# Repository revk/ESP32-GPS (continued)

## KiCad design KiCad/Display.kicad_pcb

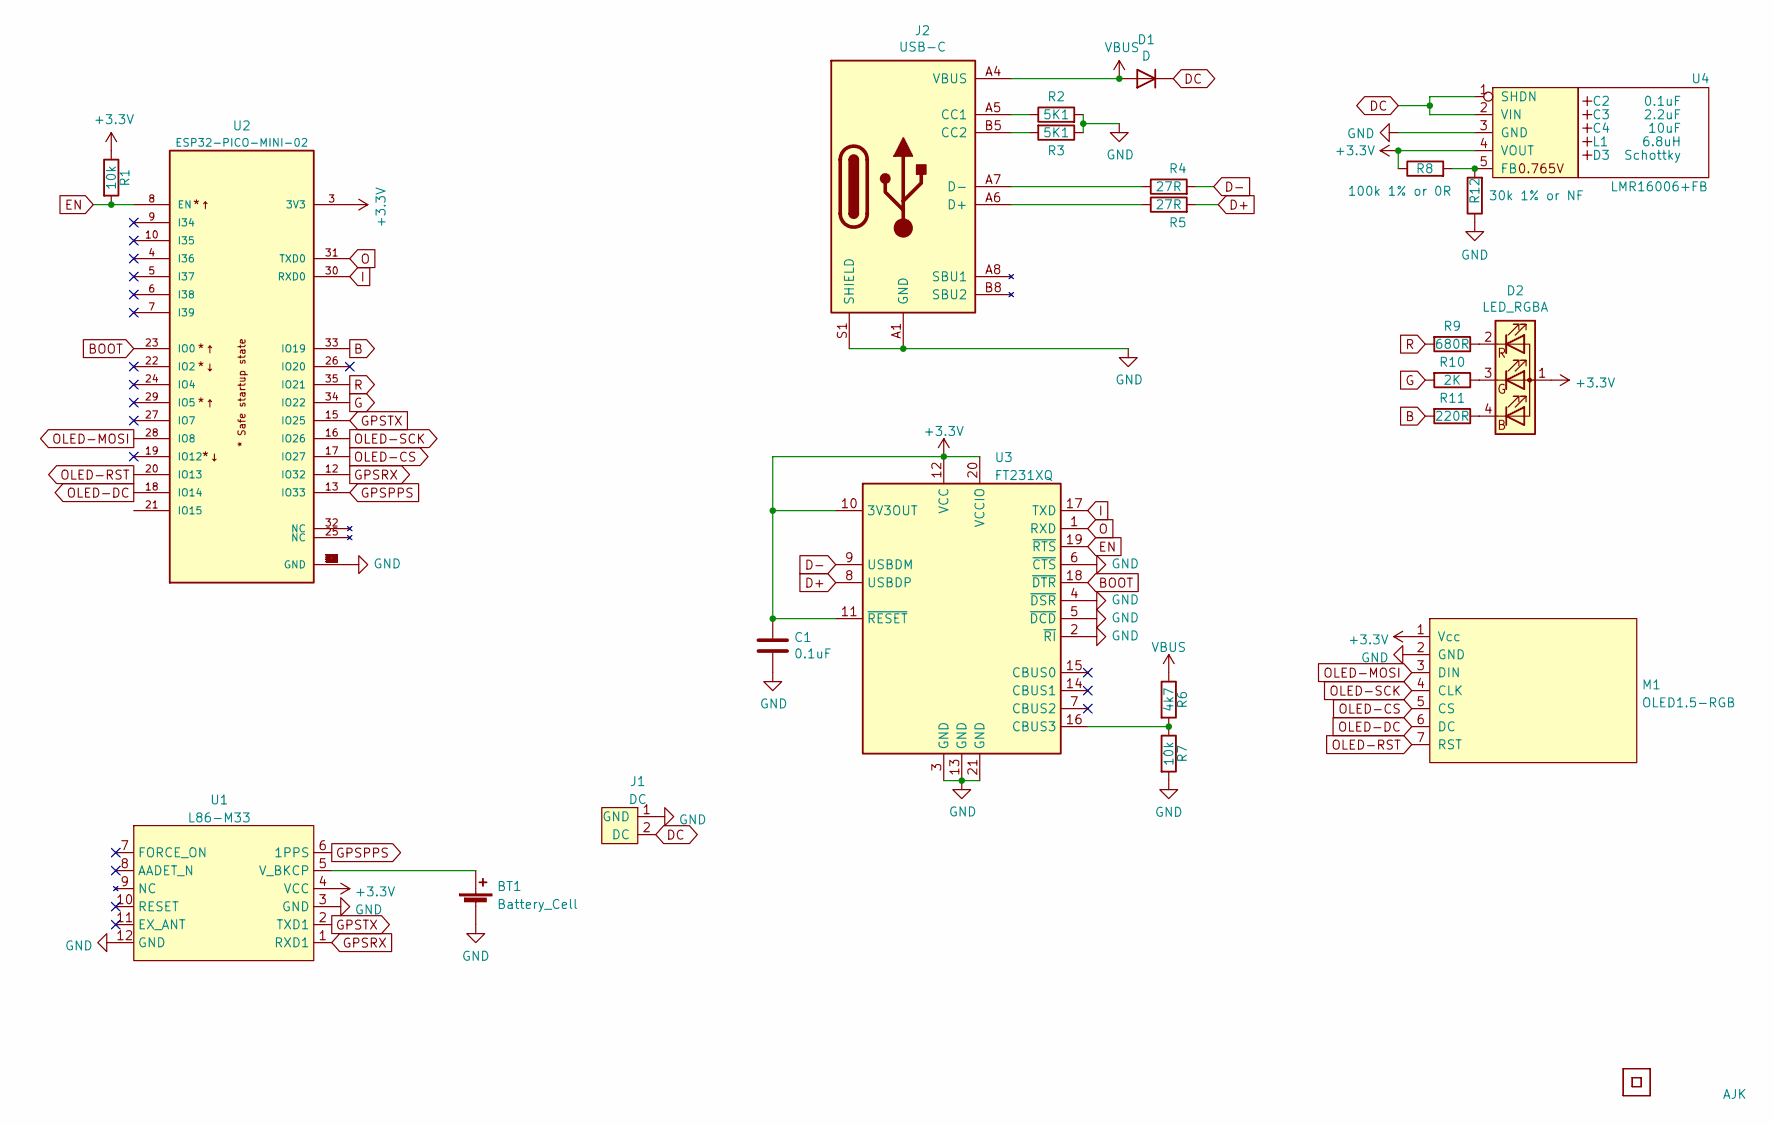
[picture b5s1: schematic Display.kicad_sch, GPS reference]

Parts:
BT1: Battery_Cell; Battery-Holder-2032
C1: 0.1uF; C_0603
C2: 0.1uF; Hidden
C3: 2.2uF; Hidden
C4: 10uF; Hidden
D1: D; D_1206
D2: LED_RGBA; LED-RGB-1.6x1.6
D3: Schottky; Hidden; Part No CD1206-B2100
J1: DC; Molex_MiniSPOX_H2RA
J2: USB-C; USC16-TR-Round
L1: 6.8uH; Hidden; Part No TYA4020
Logo2: AJK
M1: OLED1.5-RGB
R1, R7: 10k; R_0603
R2, R3: 5K1; R_0603
R4, R5: 27R; R_0603
R6: 4k7; R_0603
R8: 100k 1% or 0R; R_0603
R9: 680R; R_0603
R10: 2K; R_0603
R11: 220R; R_0603
R12: 30k 1% or NF; R_0603
U1: L86-M33
U2: ESP32-PICO-MINI-02; PARTREV v1.0
U3: FT231XQ; QFN-20-1EP_4x4mm_P0.5mm_EP2.5x2.5mm
U4: LMR16006+FB; RegulatorBlockFB; Part No LMR16006YQ3
U5: QR; QR-SS

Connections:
+3V3: C1.1, D2.1 (A), M1.1 (Vcc), R1.1, R8.1, U1.4 (VCC), U2.3 (3V3), U3.10 (3V3OUT), U3.11 (~RESET), U3.12 (VCC), U3.20 (VCCIO), U4.4 (VOUT)
B: R11.2, U2.33 (IO19)
BOOT: U2.23 (IO0), U3.18 (~DTR)
D+: R5.2, U3.8 (USBDP)
D-: R4.2, U3.9 (USBDM)
DC: D1.1 (K), J1.2 (DC), U4.1 (SHDN), U4.2 (VIN)
EN: R1.2, U2.8 (EN), U3.19 (~RTS)
G: R10.2, U2.34 (IO22)
GND: BT1.2 (-), C1.2, J1.1 (GND), J2.A1 (GND), J2.A12 (GND), J2.B1 (GND), J2.B12 (GND), J2.S1 (SHIELD), M1.2 (GND), R2.2, R3.1, R7.2, R12.1, U1.3 (GND), U1.12 (GND), U2.1 (GND), U2.2 (GND), U2.11 (GND), U2.14 (GND), U2.36 (GND), U2.37 (GND), U2.38 (GND), U2.39 (GND), U2.40 (GND), U2.41 (GND), U2.42 (GND), U2.43 (GND), U2.44 (GND), U2.45 (GND), U2.46 (GND), U2.47 (GND), U2.48 (GND), U2.49 (GND), U2.50 (GND), U2.51 (GND), U2.52 (GND), U2.53 (GND), U3.2 (~RI), U3.3 (GND), U3.4 (~DSR), U3.5 (~DCD), U3.6 (~CTS), U3.13 (GND), U3.21 (GND), U4.3 (GND)
GPSRX: U1.1 (RXD1), U2.12 (IO32)
GPSTX: U1.2 (TXD1), U2.15 (IO25)
I: U2.30 (RXD0), U3.17 (TXD)
unnamed: BT1.1 (+), U1.5 (V_BKCP)
unnamed: D2.2 (RK), R9.1
unnamed: D2.3 (GK), R10.1
unnamed: D2.4 (BK), R11.1
unnamed: J2.A5 (CC1), R2.1
unnamed: J2.A6 (D+), J2.B6 (D+), R5.1
unnamed: J2.A7 (D-), J2.B7 (D-), R4.1
unnamed: J2.B5 (CC2), R3.2
unnamed: R6.2, R7.1, U3.16 (CBUS3)
unnamed: R8.2, R12.2, U4.5 (FB)
O: U2.31 (TXD0), U3.1 (RXD)
OLED-CS0: M1.5 (CS), U2.17 (IO27)
OLED-DC: M1.6 (DC), U2.18 (IO14)
OLED-MOSI: M1.3 (DIN), U2.28 (IO8)
OLED-RST: M1.7 (RST), U2.20 (IO13)
OLED-SCLK: M1.4 (CLK), U2.16 (IO26)
R: R9.2, U2.35 (IO21)
TICK: U1.6 (1PPS), U2.13 (IO33)
VBUS: D1.2 (A), J2.A4 (VBUS), J2.A9 (VBUS), J2.B4 (VBUS), J2.B9 (VBUS), R6.1

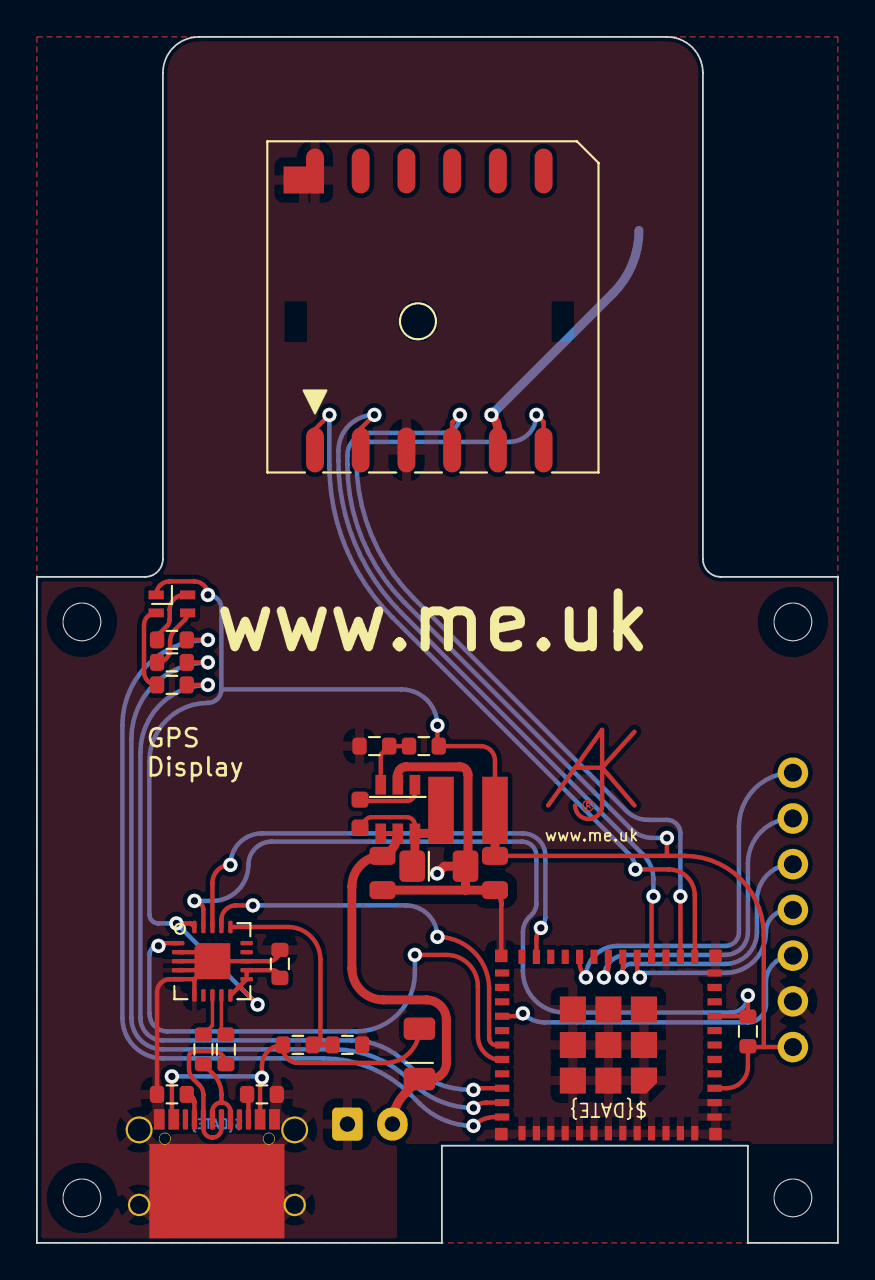
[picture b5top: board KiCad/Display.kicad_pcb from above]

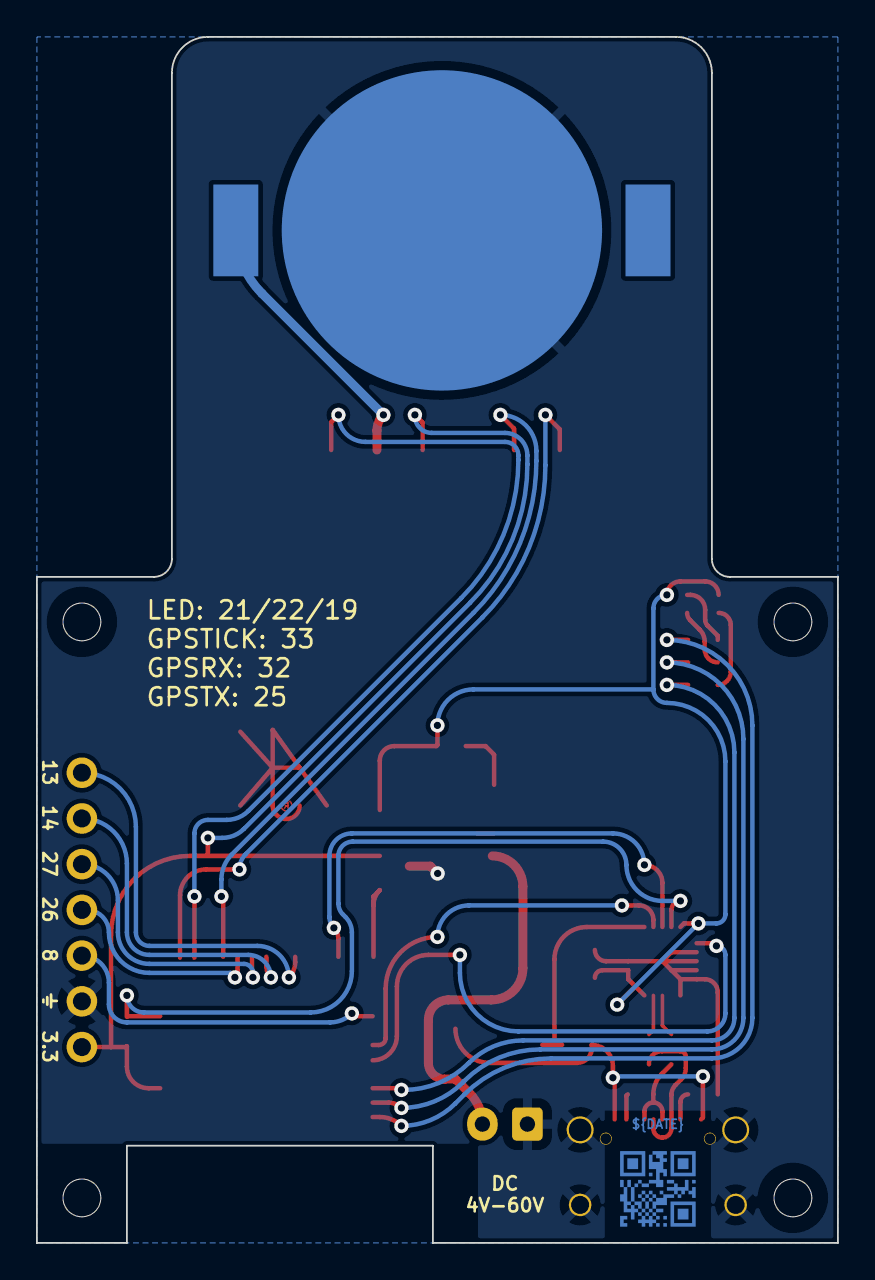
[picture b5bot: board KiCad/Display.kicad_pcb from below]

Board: 2 copper layers, 44.5 x 67.0 mm, 30 parts (2 on the bottom side), 31 nets.

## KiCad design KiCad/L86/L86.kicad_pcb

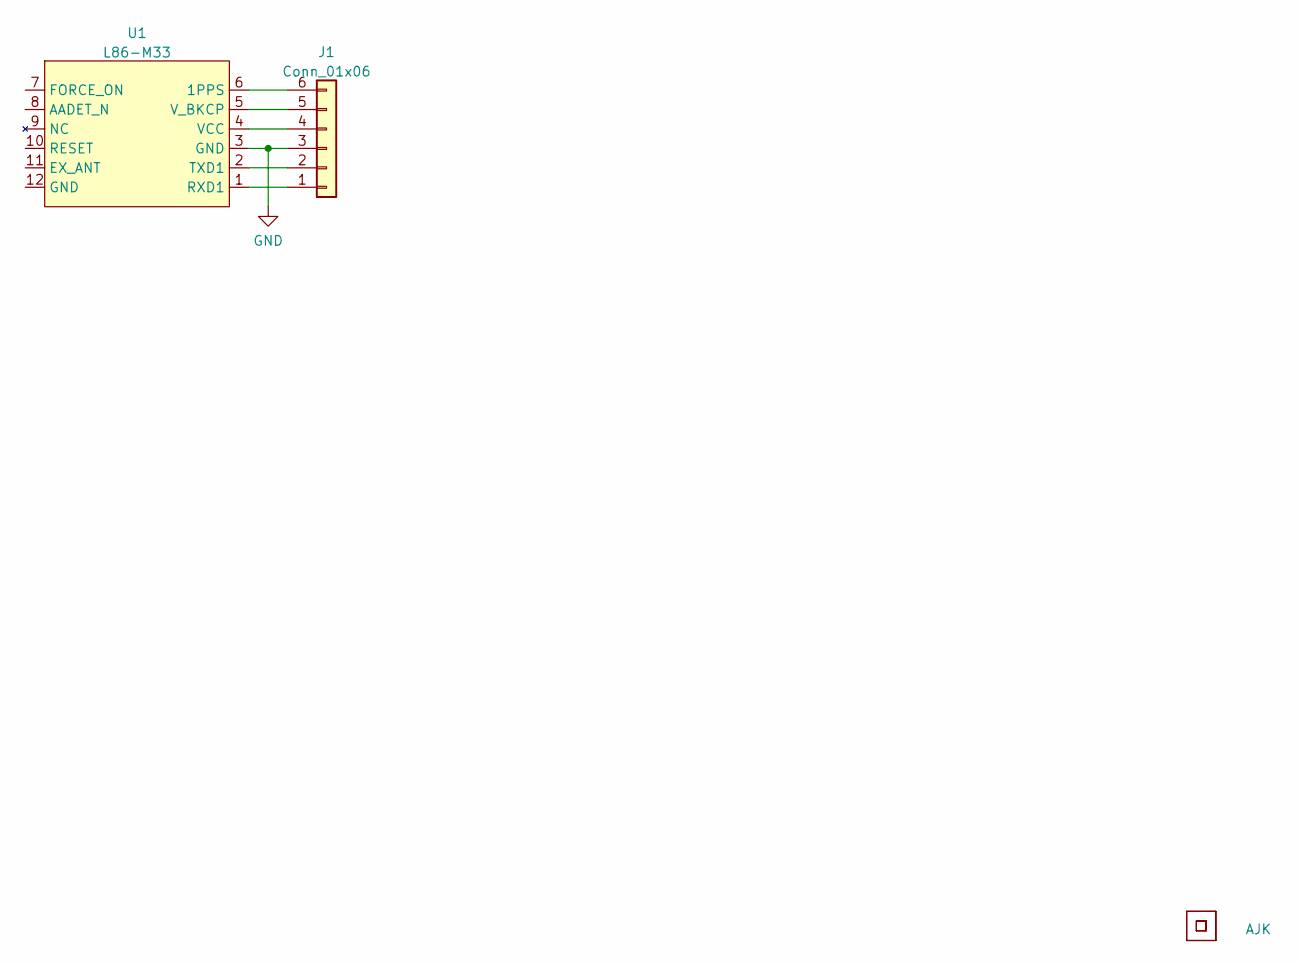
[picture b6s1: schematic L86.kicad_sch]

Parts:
J1: Conn_01x06; Molex_MiniSPOX_H6RA
Logo1: AJK
U1: L86-M33
U2: QR; QR-GPS

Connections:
GND: J1.3, U1.3 (GND)
unnamed: J1.1, U1.1 (RXD1)
unnamed: J1.2, U1.2 (TXD1)
unnamed: J1.4, U1.4 (VCC)
unnamed: J1.5, U1.5 (V_BKCP)
unnamed: J1.6, U1.6 (1PPS)

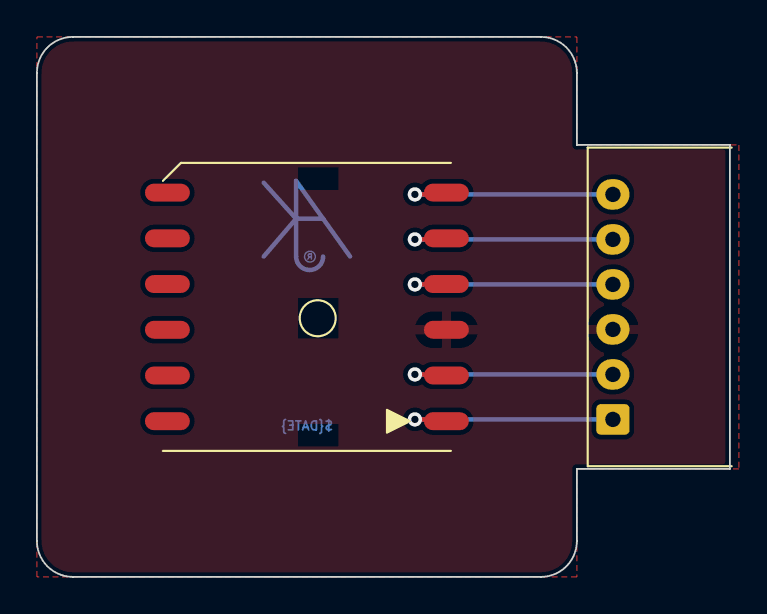
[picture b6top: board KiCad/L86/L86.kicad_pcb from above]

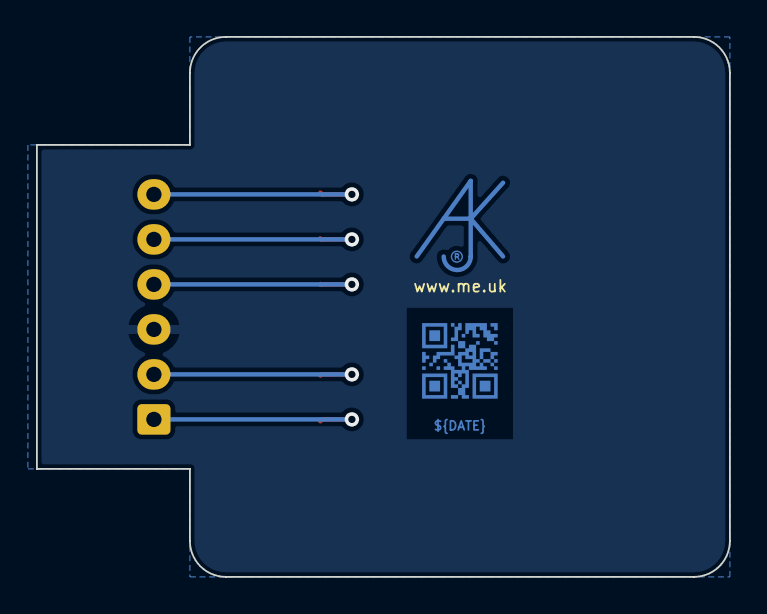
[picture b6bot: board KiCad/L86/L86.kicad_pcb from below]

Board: 2 copper layers, 38.5 x 30.0 mm, 4 parts (2 on the bottom side), 6 nets.

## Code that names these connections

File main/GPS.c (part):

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   if (!err)
      err = uart_param_config (gpsuart, &uart_config);
   if (!err)
      err = uart_set_pin (gpsuart, gpstx.num, gpsrx.num, -1, -1);
   if (!err)
      err = uart_driver_install (gpsuart, 1024, 0, 0, NULL, 0);
   if (err)
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      delay = up + 5;
      return;
   }
   if (!(b.sdpresent = revk_gpio_get (sdcd)))
   {
      ESP_LOGI (TAG, "No upload as no card");
      delay = up + 10;
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      }
   }
   esp_err_t ret;
   revk_gpio_input (sdcd);
   revk_gpio_input (sdcd);
   sdmmc_slot_config_t slot = SDMMC_SLOT_CONFIG_DEFAULT ();
   slot.clk = sdclk.num;
   slot.cmd = sdcmd.num;
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            jo_string (j, "action", cardstatus = revk_shutting_down (NULL) ? "Card dismounted for shutdown" : "Remove card");
            revk_info ("SD", &j);
            b.dodismount = 0;
            while ((b.sdpresent = revk_gpio_get (sdcd)))
               wait (1);
            continue;
         }
         if (!(b.sdpresent = revk_gpio_get (sdcd)))
         {                      // No card
            jo_t j = jo_object_alloc ();
            jo_string (j, "error", cardstatus = "Card not present");
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            revk_enable_wifi ();
            revk_enable_ap ();
            revk_enable_settings ();
            while (!(b.sdpresent = revk_gpio_get (sdcd)))
               wait (1);        // Waiting for card inserted
         }
         if (!wifidebug && (pos[0] || pos[1] || pos[2]) && (home[0] || home[1] || home[2]) && !b.home)
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         while (!b.doformat && !b.dodismount)
         {
            rgbsd = (o ? 'G' : 'Y');
            if (!(b.sdpresent = revk_gpio_get (sdcd)))
            {                   // card removed
               b.dodismount = 1;
               break;
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   }
   if (pwr.set && (usb.set || (charging.set
#ifdef  CONFIG_IDF_TARGET_ESP32S3
                               && charging.num <= 21
#endif
                   )))
      revk_web_setting (req, "Power down", "powerman");
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   {
      int bat = 100 * 2 * (adc[0] - 3.3);
      if (bat < 0)
         bat = 0;
      if (bat > 100)
         bat = 100;
      jo_int (j, "bat", bat);
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   revk_start ();
   revk_gpio_input (button);
   revk_gpio_input (usb);
   revk_gpio_input (charging);
   if (pwr.set)
   {
      revk_gpio_output (pwr, 1);
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   if (leds && rgb.set)
   {
      led_strip_config_t strip_config = {
         .strip_gpio_num = rgb.num,
         .max_leds = leds,
         .color_component_format = LED_STRIP_COLOR_COMPONENT_FMT_GRB,
         .led_model = LED_MODEL_WS2812, // LED strip model
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         revk_task ("RGB", rgb_task, NULL, 4);
   }
   // Main task...
   revk_gpio_input (gpstick);
   gps_connect (gpsbaud);
   acc_init ();
   revk_task ("NMEA", nmea_task, NULL, 5);
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         busy = up;
      if (revk_gpio_get (button))
         b.flash = b.waypoint = 1;
      charge = (charge << 1) | revk_gpio_get (charging);
      b.battery = ((charge == 0 || charge == 255) ? 1 : 0);
      b.charging = (charge == 255 ? 1 : 0);
      b.usb = revk_gpio_get (usb);
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         busy = up;
      if (!revk_shutting_down (NULL) && powerman && pwr.set && ((usb.set && !b.usb) || (charging.set && !b.charging && adc[0] < 3.8
#ifdef  CONFIG_IDF_TARGET_ESP32S3
                                                                                        && charging.num <= 21
#endif
                                                                )) && busy + (b.sdpresent && status.fixmode >= 3 ? 60 : 600) < up)
         revk_restart (1, "Power down");
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   sleep (2);
   if (powerman && pwr.set && ((usb.set && !b.usb) || (charging.set && !b.charging && adc[0] < 3.8
#ifdef  CONFIG_IDF_TARGET_ESP32S3
                                                       && charging.num <= 21
#endif
                               )))
   {                            // Deep sleep
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         REVK_ERR_CHECK (esp_sleep_enable_ext0_wakeup (usb.num, 1 - usb.invert));
      } else
      {                         // Charging based
         rtc_gpio_set_direction_in_sleep (charging.num, RTC_GPIO_MODE_INPUT_ONLY);
         rtc_gpio_pullup_en (charging.num);
         rtc_gpio_pulldown_dis (charging.num);
         REVK_ERR_CHECK (esp_sleep_enable_ext0_wakeup (charging.num, 1 - charging.invert));
      }
      sleep (1);
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
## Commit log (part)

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2024-01-17 Library update
2024-01-17 checkpoint
2024-01-17 release
2024-01-17 Manual for `home`
2024-01-17 Format
2024-01-18 Test
2024-01-18 Move charger input
2024-01-18 RTC pins
2024-01-18 Tweak
2024-01-18 Fading blink
2024-01-18 Rework
2024-01-18 Tidy
2024-01-18 Started on 3D
2024-01-19 Buy link
2024-01-20 L86 STL
2024-01-20 Neater STL
2024-01-20 Position adjust
2024-01-21 Started on postcode logic
2024-01-21 Postcode database
2024-01-21 Close
2024-01-21 Close on postcode
2024-01-22 Revised logic - postcode table now using lat/lon
2024-01-22 Silly
2024-01-22 Space in postcode
2024-01-22 postcodes
2024-01-22 powerstop
2024-01-22 Notes
2024-01-22 Postcode
2024-01-22 Email
2024-01-23 ODO check
2024-01-24 Tidy for Mac
2024-01-24 GPIO
2024-01-24 Power
2024-01-24 Working on power management
2024-01-25 Nope
2024-01-25 Clarify odo
2024-01-28 Extra ESD so GPIO0 can be used as a button
2024-01-30 Multi file
2024-01-30 waypoint
2024-01-31 Tidy CSV
2024-01-31 Cleaner tracks
2024-01-31 Tool
2024-01-31 FFS USB not working
2024-02-05 beta
2024-03-04 Tidy PCB
2024-03-16 Documented example plastic case option
    Makes sense to collect links for suitable tested accessories so
    people know what works.
2024-05-06 Update for library
2024-05-06 Zap and re do
2024-05-06 Back
2024-06-30 New headers
2024-11-24 Resistors
2024-12-18 MMC mode SD
2025-01-23 PCB Update
2026-02-13 submodule
2026-02-15 Codeberg
2026-02-19 duplicate
